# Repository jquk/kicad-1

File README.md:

# kicad-1
Kicad practice projects

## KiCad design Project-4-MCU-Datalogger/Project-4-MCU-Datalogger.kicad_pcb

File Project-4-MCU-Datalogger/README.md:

# Non Kicad Standard Library Components:
- **DS1337S+**:
  - Description: Real Time Clock (RTC) IC Clock/Calendar I2C, 2-Wire Serial 8-SOIC (0.154", 3.90mm Width).
  - Package Type:  SOIC-8
  - URL: `https://www.snapeda.com/parts/DS1337S+/Maxim%20Integrated%20Products/view-part/?ref=search&t=ds1337s&ab_test_case=b`

- **ATMEGA328P-AU**:
  - Description: MCU 8-bit - AVR ATmega Family ATmega328 Series Microcontrollers - 20 MHz - 32 KB - 2 KB - 32 Pins.
  - Package Type:  TQFP-32.
  - URL: `https://www.snapeda.com/parts/ATMEGA328P-AU/MICROCHIP%20TECH./view-part/?ref=search&t=atmega328p-au&ab_test_case=b`

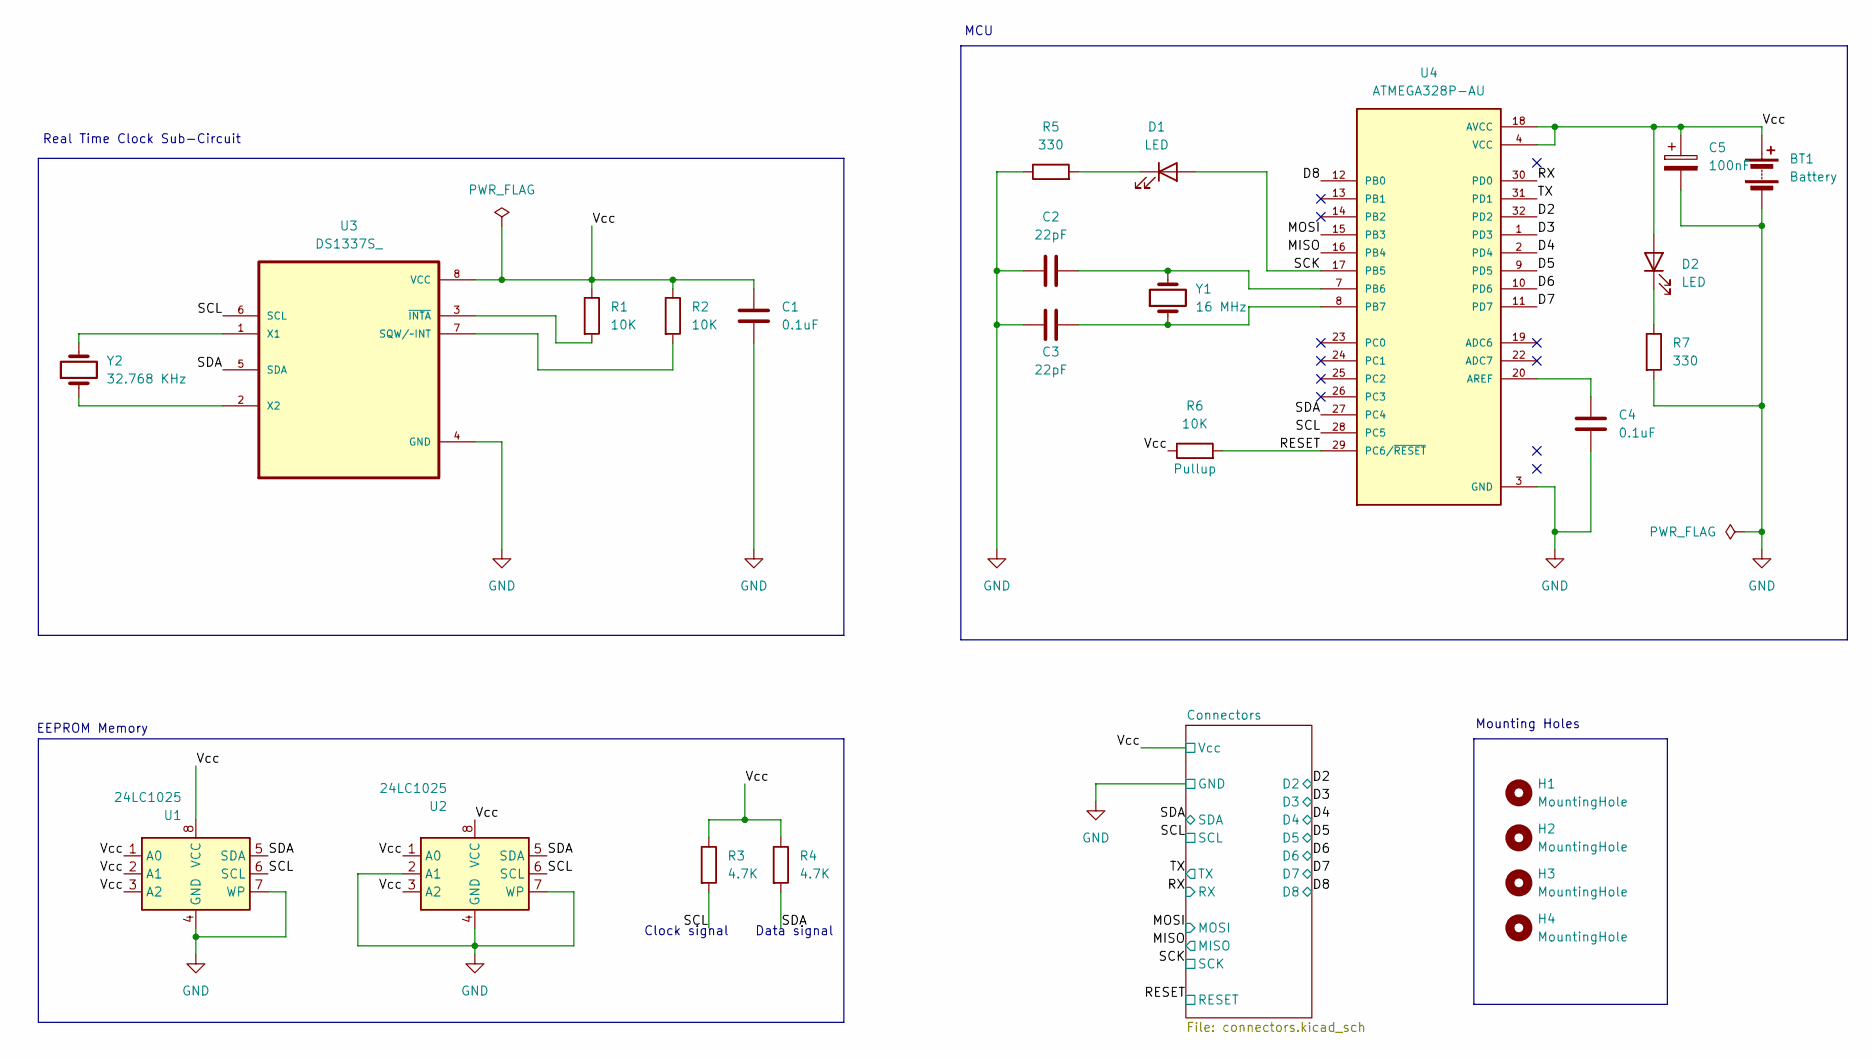
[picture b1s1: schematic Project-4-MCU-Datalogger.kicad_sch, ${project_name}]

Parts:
BT1: Battery; PinHeader_1x02_P2.54mm_Vertical
C1, C4: 0.1uF; C_0805_2012Metric
C2, C3: 22pF; C_0805_2012Metric
C5: 100nF; C_0805_2012Metric
D1, D2: LED; LED_0805_2012Metric
H1, H2, H3, H4: MountingHole; MountingHole_2.1mm
R1, R2, R6: 10K; R_0805_2012Metric
R3, R4: 4.7K; R_0805_2012Metric
R5, R7: 330; R_0805_2012Metric
U1, U2: 24LC1025; SOIC-8_5.3x5.3mm_P1.27mm
U3: DS1337S_; SOIC127P600X175-8N
U4: ATMEGA328P-AU; QFP80P900X900X120-32N; PARTREV 8271A
Y1: 16 MHz; Crystal_SMD_5032-2Pin_5.0x3.2mm_HandSoldering
Y2: 32.768 KHz; Crystal_SMD_5032-2Pin_5.0x3.2mm_HandSoldering

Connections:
/D2: U4.32 (PD2); also elsewhere on the board
/D3: U4.1 (PD3); also elsewhere on the board
/D4: U4.2 (PD4); also elsewhere on the board
/D5: U4.9 (PD5); also elsewhere on the board
/D6: U4.10 (PD6); also elsewhere on the board
/D7: U4.11 (PD7); also elsewhere on the board
/D8: U4.12 (PB0); also elsewhere on the board
/MISO: U4.16 (PB4); also elsewhere on the board
/MOSI: U4.15 (PB3); also elsewhere on the board
/RESET: R6.2, U4.29 (PC6/~RESET); also elsewhere on the board
/RX: U4.30 (PD0); also elsewhere on the board
/SCK: D1.2 (A), U4.17 (PB5); also elsewhere on the board
/SCL: R3.2, U1.6 (SCL), U2.6 (SCL), U3.6 (SCL), U4.28 (PC5); also elsewhere on the board
/SDA: R4.2, U1.5 (SDA), U2.5 (SDA), U3.5 (SDA), U4.27 (PC4); also elsewhere on the board
/TX: U4.31 (PD1); also elsewhere on the board
/Vcc: BT1.1 (+), C1.1, C5.1, D2.2 (A), R1.1, R2.1, R3.1, R4.1, R6.1, U1.1 (A0), U1.2 (A1), U1.3 (A2), U1.8 (VCC), U2.1 (A0), U2.3 (A2), U2.8 (VCC), U3.8 (VCC), U4.4 (VCC), U4.18 (AVCC); also elsewhere on the board
GND: BT1.2 (-), C1.2, C2.1, C3.1, C4.1, C5.2, R5.1, R7.2, U1.4 (GND), U1.7 (WP), U2.2 (A1), U2.4 (GND), U2.7 (WP), U3.4 (GND), U4.3 (GND), U4.5 (GND), U4.21 (GND); also elsewhere on the board
unnamed: D1.1 (K), R5.2
unnamed: D2.1 (K), R7.1
unnamed: R2.2, U3.7 (SQW/~INT)
unnamed: U3.1 (X1), Y2.2
unnamed: U3.2 (X2), Y2.1
unnamed: R1.2, U3.3 (~INTA)
unnamed: C4.2, U4.20 (AREF)
unnamed: C2.2, U4.7 (PB6), Y1.2
unnamed: C3.2, U4.8 (PB7), Y1.1
VCC: U4.6 (VCC)

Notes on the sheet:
Real Time Clock Sub-Circuit
Data signal
Mounting Holes
Clock signal
MCU
EEPROM Memory

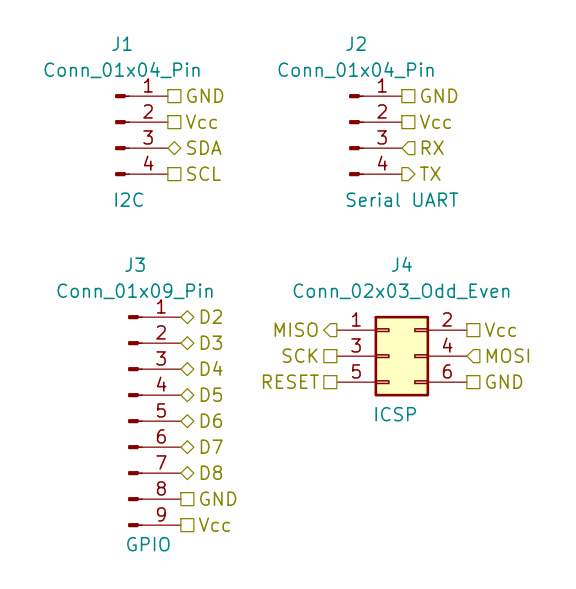
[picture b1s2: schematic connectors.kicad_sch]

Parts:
J1, J2: Conn_01x04_Pin; PinHeader_1x04_P2.54mm_Vertical
J3: Conn_01x09_Pin; PinHeader_1x09_P2.54mm_Vertical
J4: Conn_02x03_Odd_Even; PinHeader_2x03_P2.54mm_Vertical

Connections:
/D2: J3.1; also elsewhere on the board
/D3: J3.2; also elsewhere on the board
/D4: J3.3; also elsewhere on the board
/D5: J3.4; also elsewhere on the board
/D6: J3.5; also elsewhere on the board
/D7: J3.6; also elsewhere on the board
/D8: J3.7; also elsewhere on the board
/MISO: J4.1; also elsewhere on the board
/MOSI: J4.4; also elsewhere on the board
/RESET: J4.5; also elsewhere on the board
/RX: J2.3; also elsewhere on the board
/SCK: J4.3; also elsewhere on the board
/SCL: J1.4; also elsewhere on the board
/SDA: J1.3; also elsewhere on the board
/TX: J2.4; also elsewhere on the board
/Vcc: J1.2, J2.2, J3.9, J4.2; also elsewhere on the board
GND: J1.1, J2.1, J3.8, J4.6; also elsewhere on the board

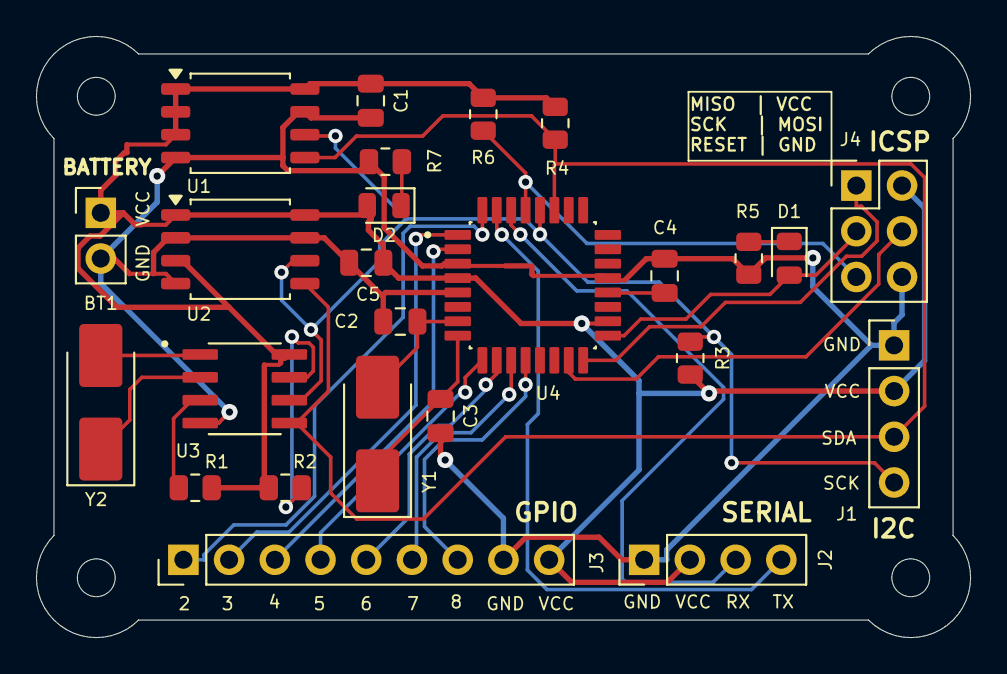
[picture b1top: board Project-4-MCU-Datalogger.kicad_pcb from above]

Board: 2 copper layers, 51.9 x 33.4 mm, 29 parts (0 on the bottom side), 26 nets.

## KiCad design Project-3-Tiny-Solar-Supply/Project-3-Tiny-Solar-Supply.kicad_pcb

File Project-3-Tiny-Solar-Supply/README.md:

# Elektor Magazine's Article and Project on Regulated Voltage Battery Output: 
`https://www.elektormagazine.com/magazine/elektor-305/62009`

## Bill of Materials
Resistors (0805, 0.125 W):
Use Kicad's standard library.
- R1, R4 = 1 MΩ
- R2 = 604 kΩ, 1%
- R3 = 10 kΩ

Capacitors
Use Kicad's standard library.
- C1 = 4.7 µF, 50 V, X7R (0805)
- C2 = 22 µF, 10 V, X7R (1206)
- C3 = 10 pF, 50 V, X7R (0805)

Inductors
- L1 = 10 µH, 680 mA        --> Snapeda.com: `https://www.snapeda.com/parts/ASPI-0630LR-100M-T15/Abracon/view-part/?ref=search&t=abracon%20ASPI-0630LR-100M-T15&ab_test_case=b`

Semiconductors
- D1, D2 = SS14 (DO-214AC)  --> Snapeda.com: `https://www.snapeda.com/parts/SS14/ON/view-part/?ref=search&t=ss14&ab_test_case=b`
- IC1* = AP3015 or AP3015A  --> Snapeda.com: `https://www.snapeda.com/parts/AP3015AKTR-G1/Diodes%20Inc./view-part/?ref=search&t=AP3015AKTR-G1&ab_test_case=b`
- T1 = 2N7002 (SOT-23)      --> Standard Kicad library

Miscellaneous
- K1, K2, K3 = pin header, 1 row, 2 contacts, 2.54 mm pitch   --> Standard Kicad library
- K4 = pin header, 1 row, 2 contacts, right-angle, 2 mm pitch --> Standard Kicad library

## Description and Project Elements
`https://www.elektormagazine.com/labs/tiny-solar-supply`
Tiny Solar Supply
A tiny solar power supply similar to those found in garden lights, but with a voltage regulator.

Need a regulated voltage out of an AA(A) (rechargeable) battery? Then this tiny boost converter might just be what you are looking for.

We used to have two solar-powered garden light strings from Ikea lighting up our garden at night. They worked very well, but over the years the colorful lights slowly disintegrated until only the solar panels were left over. As these solar panels are well built, waterproof and all that, I decided to keep them to see if I couldn’t do something else with them.

During the day, the solar panel charges a single 1.2 V Ni-MH AA rechargeable battery. When it gets dark, charging stops, and a tiny boost converter switches on to pump up the battery voltage to something suitable for powering a string of white LEDs. This is nice, but unregulated as the output voltage depends on the load.

This little circuit turns the 1.2 V at its input into a regulated 3.3 V suitable for e.g. a microcontroller-based something. The schematic is attached below. The heart of the circuit is IC1, an AP3015 micro power step-up DC/DC converter from Diodes, Inc. Its A-version works with input voltages as low as 1 V (and up to 12 V) and can deliver 100 mA. The non-A version starts at 1.2 V but can supply up to 350 mA. The output voltage is determined by the ratio of R1 and R2:

VOUT = 1.23 × (1 + R1/R2)

With the given values, the output voltage is (almost) 3.3 V. L1, D1, and C1 to C3 are the recommended components needed to make the boost converter work. L1 can be one of those inductors that look like a resistor as long as it can pass at least the maximum load current.

When the solar panel (on K4) is getting light, it charges the battery (connected to K2) through diode D2. At the same time, it pulls the gate of T1 up. This makes T1 conduct, pulling the shutdown pin of IC1 low, turning it off. When the output voltage of the solar panel drops too low, battery charging stops, T1 switches off and IC1 switches on. If you don’t want this automatic switching, then leave T1 out. An On/Off switch or jumper connected to K3 gives you a bit more control over the circuit.

I designed a little PCB for the circuit that fits nicely inside the old Ikea solar panel. Today, this model is obsolete, but I am sure it will fit in other types too.

Design files are attached below.

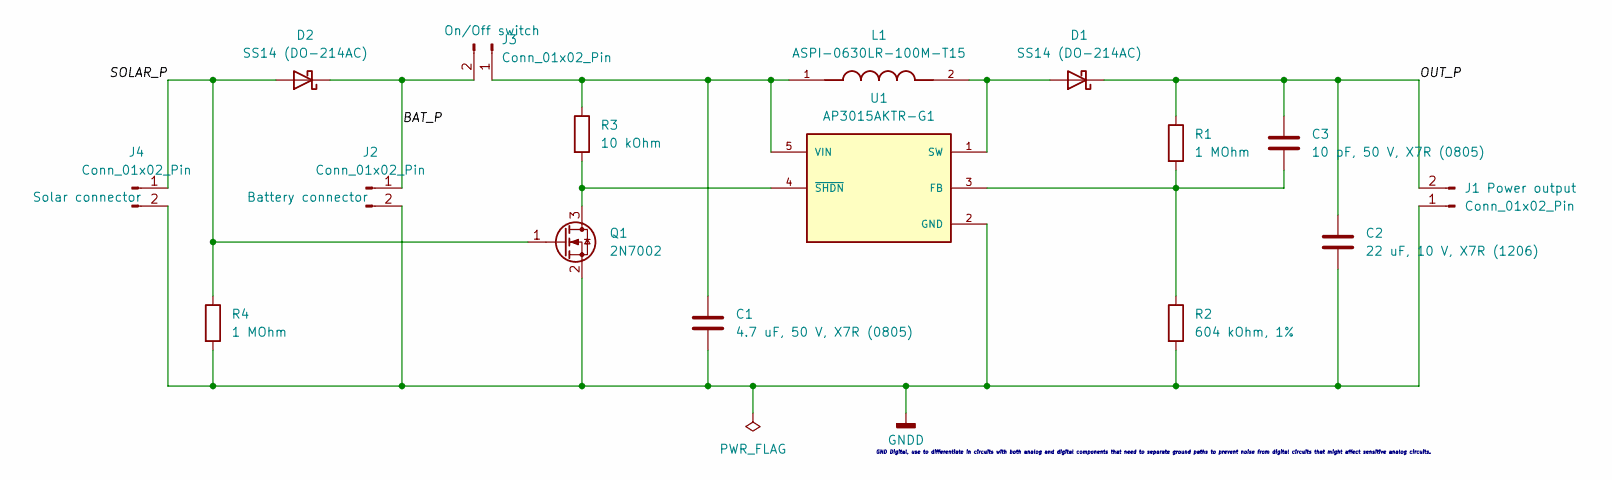
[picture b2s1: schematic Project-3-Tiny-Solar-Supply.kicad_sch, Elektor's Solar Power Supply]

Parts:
C1: 4.7 uF, 50 V, X7R (0805); C_0805_2012Metric
C2: 22 uF, 10 V, X7R (1206); C_1206_3216Metric
C3: 10 pF, 50 V, X7R (0805); C_0805_2012Metric
D1, D2: SS14 (DO-214AC); DO-214AC
J1, J2, J4: Conn_01x02_Pin; PinHeader_1x02_P2.54mm_Horizontal
J3: Conn_01x02_Pin; SW_DIP_SPSTx01_Slide_9.78x4.72mm_W7.62mm_P2.54mm
L1: ASPI-0630LR-100M-T15; IND_ASPI-0630LR-100M-T15; PARTREV B
Q1: 2N7002; SOT-23
R1, R4: 1 MOhm; R_0805_2012Metric
R2: 604 kOhm, 1%; R_0805_2012Metric
R3: 10 kOhm; R_0805_2012Metric
U1: AP3015AKTR-G1; SOT95P280X145-5N; PARTREV 1.4

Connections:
/BAT_P: D2.1 (K), J2.1, J3.2
/OUT_P: C2.1, C3.1, D1.1 (K), J1.2, R1.1
/SOLAR_P: D2.2 (A), J4.1, Q1.1 (G), R4.1
GNDD: C1.2, C2.2, J1.1, J2.2, J4.2, Q1.2 (S), R2.2, R4.2, U1.2 (GND)
unnamed: D1.2 (A), L1.2, U1.1 (SW)
unnamed: C1.1, J3.1, L1.1, R3.1, U1.5 (VIN)
unnamed: Q1.3 (D), R3.2, U1.4 (~SHDN)
unnamed: C3.2, R1.2, R2.1, U1.3 (FB)

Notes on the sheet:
GND Digital, use to differentiate in circuits with both analog and digital components that need to separate ground paths to prevent noise from digital circuits that might affect sensitive analog circuits.

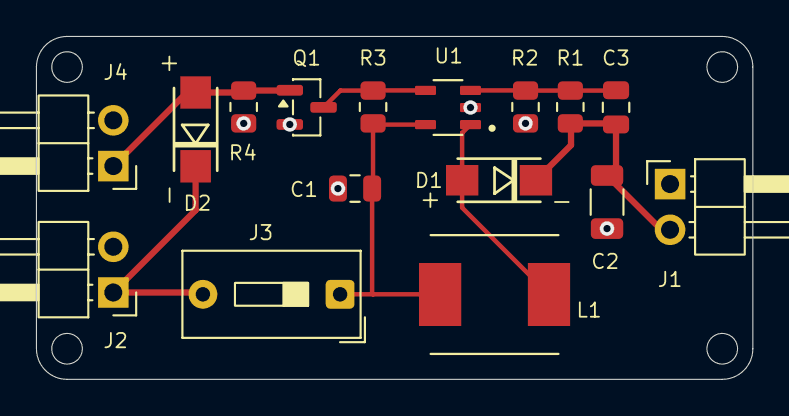
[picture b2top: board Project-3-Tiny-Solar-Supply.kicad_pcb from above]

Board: 2 copper layers, 39.8 x 19.0 mm, 16 parts (0 on the bottom side), 8 nets.

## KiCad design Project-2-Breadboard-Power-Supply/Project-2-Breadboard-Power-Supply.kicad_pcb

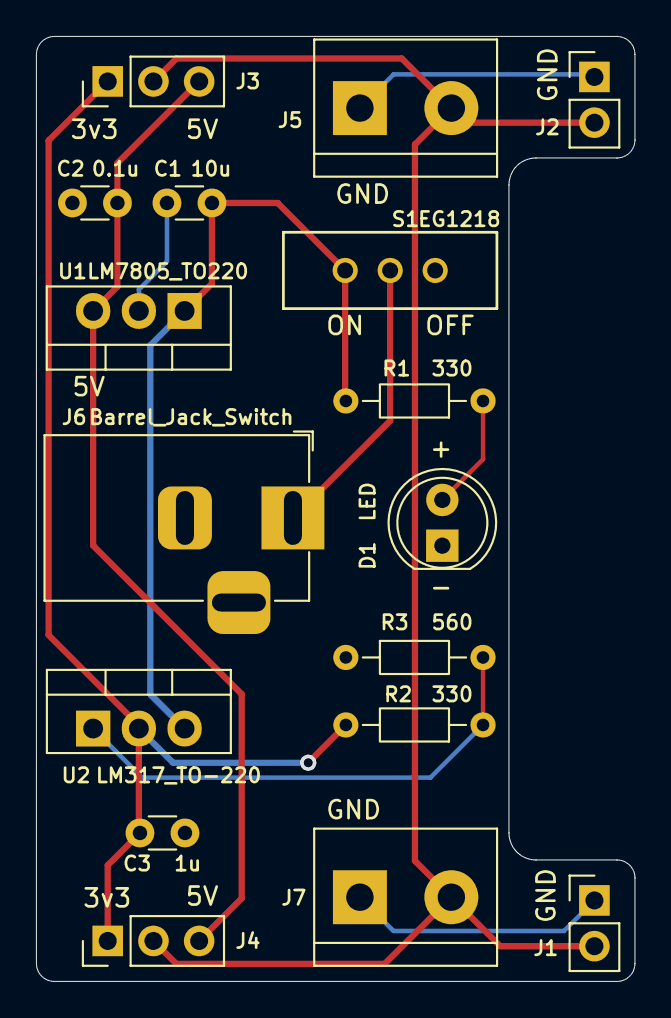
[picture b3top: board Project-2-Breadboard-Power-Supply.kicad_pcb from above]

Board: 2 copper layers, 33.2 x 52.5 mm, 17 parts (0 on the bottom side), 8 nets.

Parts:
C1: 10u; C_Disc_D3.0mm_W1.6mm_P2.50mm
C2: 0.1u; C_Disc_D3.0mm_W1.6mm_P2.50mm
C3: 1u; C_Disc_D3.0mm_W1.6mm_P2.50mm
D1: LED; LED_D5.0mm
J1, J2: Conn_01x02_Pin; PinHeader_1x02_P2.54mm_Vertical
J3, J4: Conn_01x03_Pin; PinHeader_1x03_P2.54mm_Vertical
J5, J7: Screw_Terminal_01x02; TerminalBlock_bornier-2_P5.08mm
J6: Barrel_Jack_Switch; BarrelJack_Horizontal
R1, R2: 330; R_Axial_DIN0204_L3.6mm_D1.6mm_P7.62mm_Horizontal
R3: 560; R_Axial_DIN0204_L3.6mm_D1.6mm_P7.62mm_Horizontal
S1: EG1218; SW_1218_EWI
U1: LM7805_TO220; TO-220-3_Vertical
U2: LM317_TO-220; TO-220-3_Vertical

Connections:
/3v3_net: C3.1, J3.1, J4.1, R2.2, U2.2 (VO)
/5V_net: C2.1, J3.3, J4.3, U1.3 (VO)
/12V_net: C1.1, R1.2, S1.1, U1.1 (VI), U2.3 (VI)
/PWR_input: J6.1, S1.2
/PWR_output: J1.2, J2.2, J3.2, J4.2, J5.2, J7.2
GND: C1.2, C2.2, C3.2, D1.1 (K), J1.1, J2.1, J5.1, J6.2, J6.3, J7.1, R3.1, U1.2 (GND)
unnamed: D1.2 (A), R1.1
unnamed: R2.1, R3.2, U2.1 (ADJ)

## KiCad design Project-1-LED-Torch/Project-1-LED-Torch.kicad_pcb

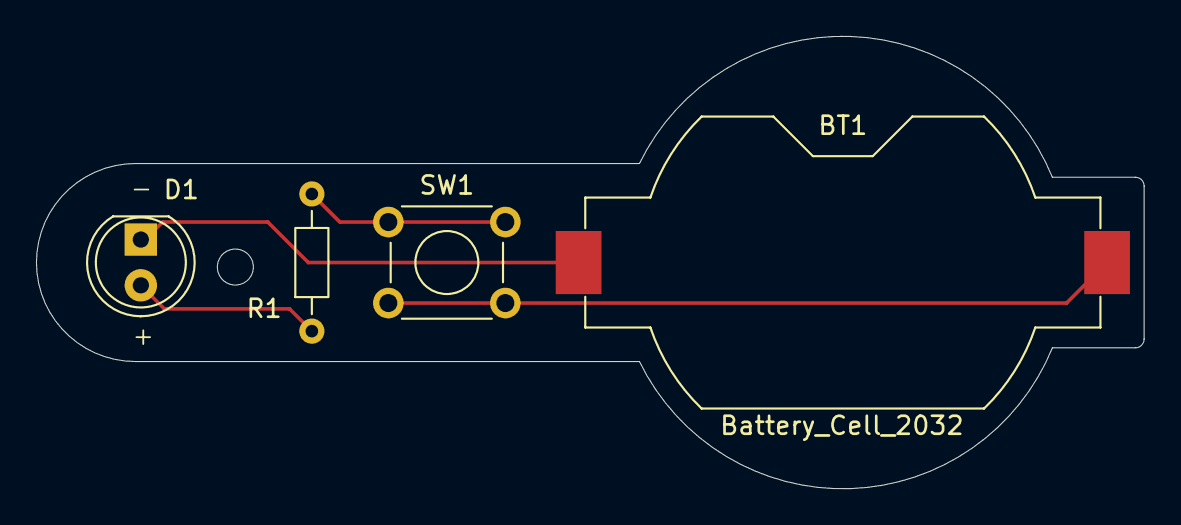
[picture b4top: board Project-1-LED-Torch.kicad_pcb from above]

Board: 2 copper layers, 61.5 x 25.1 mm, 4 parts (0 on the bottom side), 4 nets.

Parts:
BT1: Battery_Cell_2032; BatteryHolder_Keystone_1058_1x2032
D1: LED; LED_D5.0mm
R1: R; R_Axial_DIN0204_L3.6mm_D1.6mm_P7.62mm_Horizontal
SW1: SW_DPDT_x2; SW_TH_Tactile_Omron_B3F-100x

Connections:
/Battery_positive: BT1.1 (+), SW1.2 (B)
/LED_anode: D1.2 (A), R1.1
/LED_cathode: BT1.2 (-), D1.1 (K)
unnamed: R1.2, SW1.1 (A)
